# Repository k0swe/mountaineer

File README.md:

This is a build-it-yourself project at the moment. For something productized, see https://digirig.net/!

#  Mountaineer Radio Interface

This KiCAD project is a schematic for an integrated CAT and audio amateur radio interface. It's
designed with the [Lab599 Discovery TX-500](https://lab599.com/) radio in mind, but the only thing
that makes it radio-specific is the GX12 connectors for CAT and DATA. The rest of the board is a
generic USB-to-serial and audio interface and is suitable for many radios.

This is somewhat comparable to the Yaesu SCU-17 interface in that it provides both audio
and [CAT control](https://en.wikipedia.org/wiki/Computer_Aided_Transceiver). It is less like the
SignaLink USB interface which only provides audio plus a VOX-based PTT signal but not CAT control.

My design goals are to make this much like the TX-500 itself: small, lightweight and rugged enough
to be outdoors. As such, volume knobs and headphone monitor jacks are not incorporated.

Mechanical CAD drawings are hosted publicly in 
[Onshape](https://cad.onshape.com/documents/40ae2a09f3b2d7950cd3b26d/w/39e0f86d97c1d198a7f9316f/e/2142c3ad4293d2f81a75534e).

## Thank you!

I've received a lot of advice from folks about improvements to this design. Thank you to those who
have helped make this project better!

* Kari Argillander, [@teksturi](https://github.com/teksturi)
* Elías Rodríguez Martín, [@eliasrm87](https://github.com/eliasrm87)
* EEVblog Forum user [mon2](https://www.eevblog.com/forum/profile/?u=690092)
* Dave Maciorowski, [WA1JHK](https://www.qrz.com/db/WA1JHK)
* Nathan Conrad, [@pigrew](https://github.com/pigrew)
* Andreas Jochum, [@ctech4285](https://github.com/ctech4285)
* [The Gizmo Dojo](http://thegizmodojo.com/)
* [Rocky Mountain Ham Radio](https://www.rmham.org/)

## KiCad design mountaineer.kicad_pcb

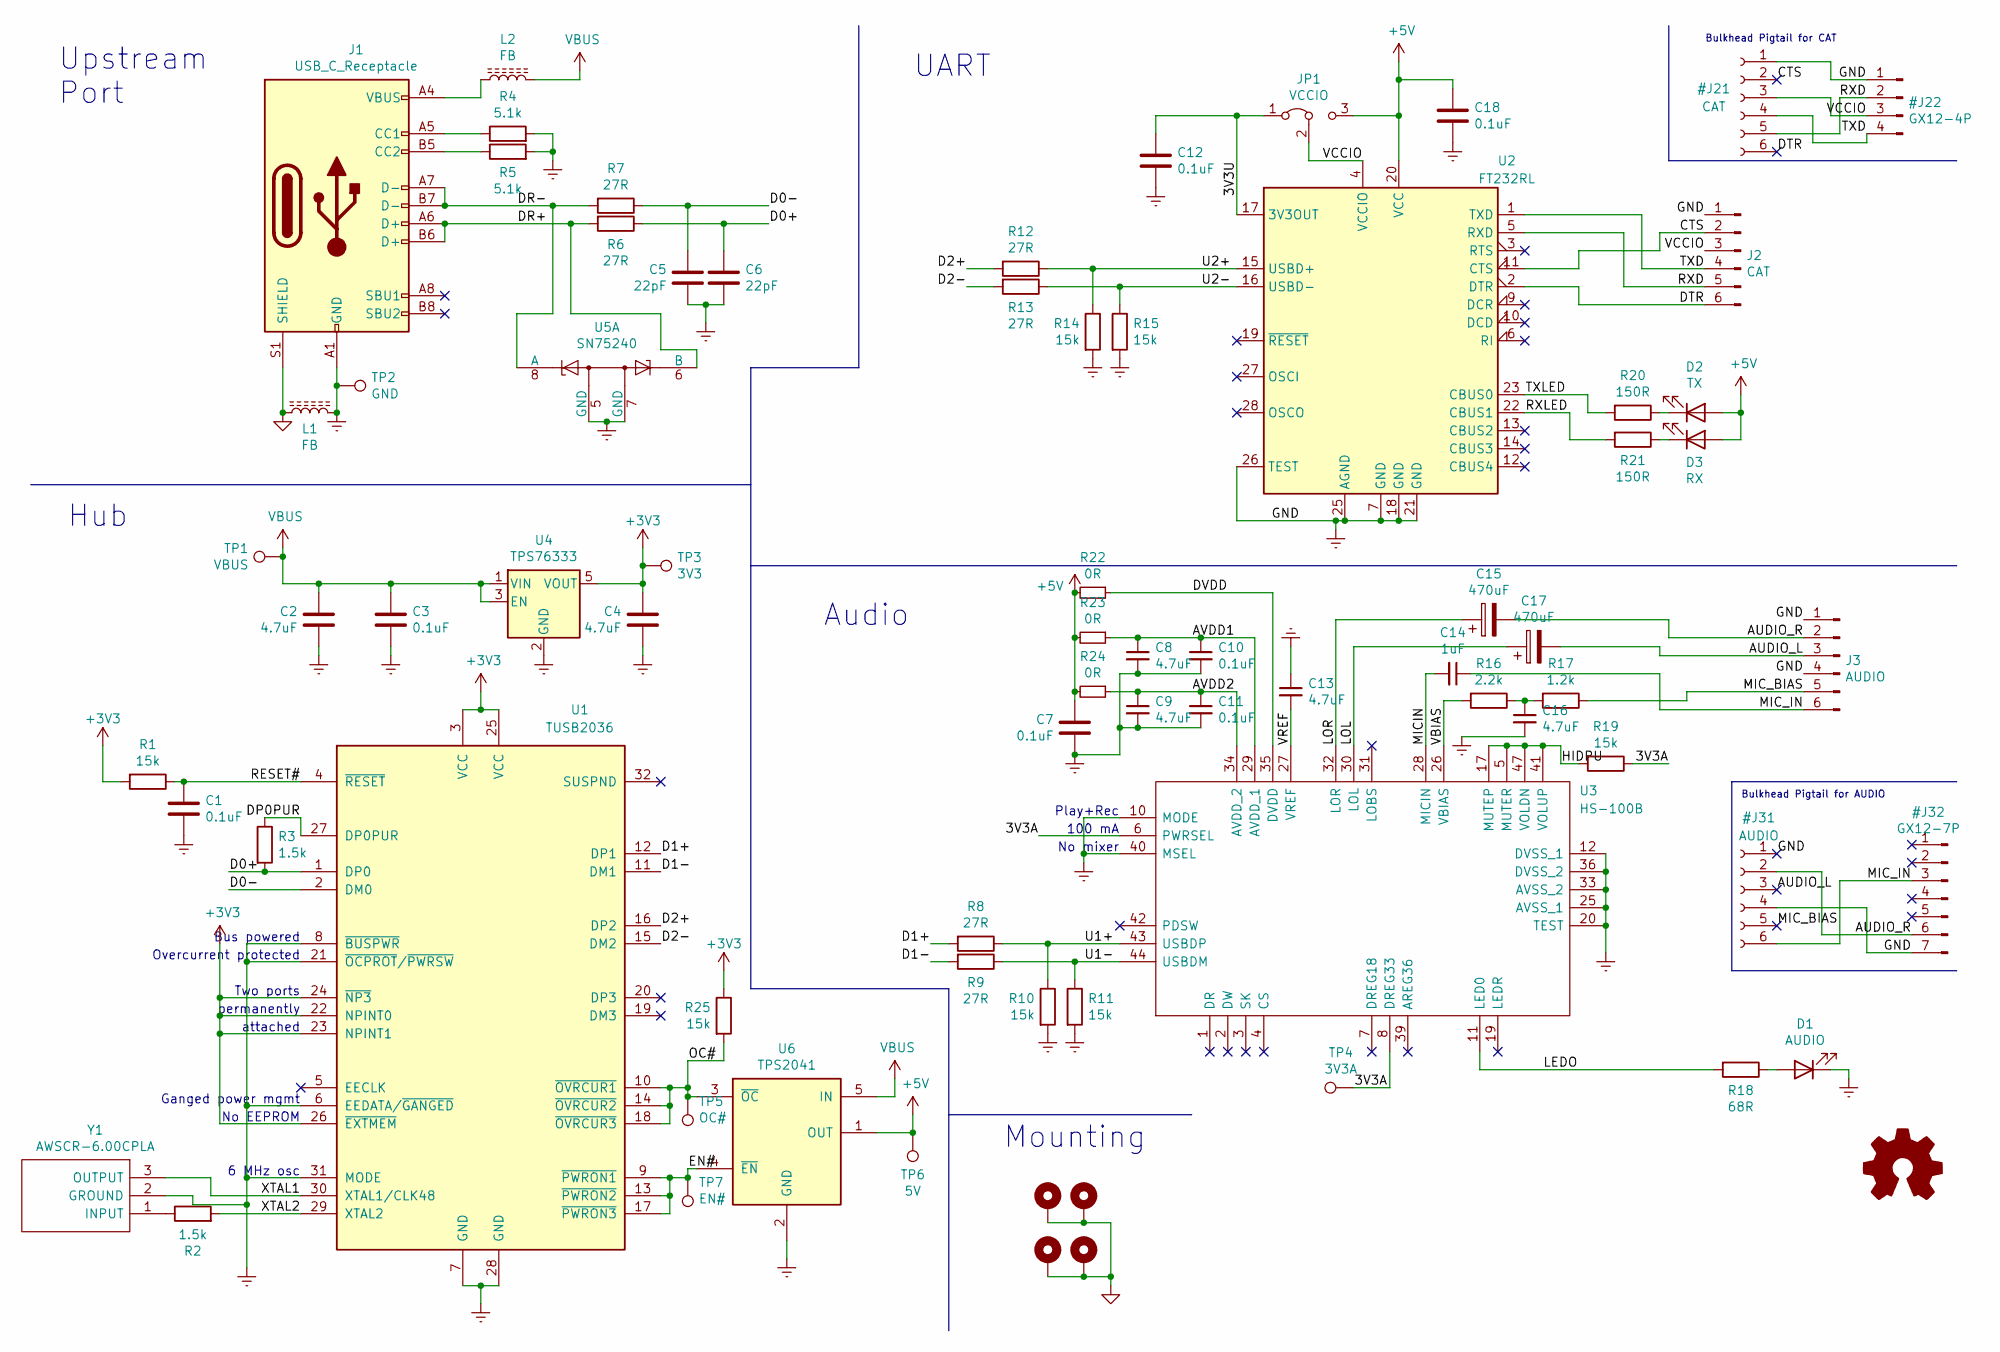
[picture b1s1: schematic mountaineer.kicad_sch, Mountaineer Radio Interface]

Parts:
C1, C3, C7, C10, C11, C12, C18: 0.1uF; C_0603_1608Metric; LCSC C1588
C2, C4, C8, C9, C13, C16: 4.7uF; C_0603_1608Metric; LCSC C19666
C5, C6: 22pF; C_0603_1608Metric; LCSC C1653
C14: 1uF; C_0603_1608Metric; LCSC C15849
C15, C17: 470uF; CAPPM7343X430N; Manufacturer_Part_Number 293D477X9010E2TE3; LCSC C232200
D1: AUDIO; LED_0603_1608Metric; LCSC C2286
D2: TX; LED_0603_1608Metric; LCSC C2286
D3: RX; LED_0603_1608Metric; LCSC C2286
H1, H2, H3, H4: MountingHole_Pad; MountingHole_2.2mm_M2_Pad
J1: USB_C_Receptacle; CUI_UJ31-CH-G-SMT-TR-67; Manufacturer_Part_Number UJ31-CH-G-SMT-TR-67
J2: CAT; JST_PH_B6B-PH-SM4-TB_1x06-1MP_P2.00mm_Vertical; Manufacturer_Part_Number B6B-PH-SM4-TB; LCSC C471518
J3: AUDIO; JST_PH_B6B-PH-SM4-TB_1x06-1MP_P2.00mm_Vertical; Manufacturer_Part_Number B6B-PH-SM4-TB; LCSC C471518
JP1: VCCIO; SolderJumper-3_P1.3mm_Bridged12_RoundedPad1.0x1.5mm
L1, L2: FB; L_0805_2012Metric; LCSC C1017
LOGO1: Logo_Open_Hardware_Small; OSHW-Logo2_9.8x8mm_Copper
R1, R10, R11, R14, R15, R19, R25: 15k; R_0603_1608Metric; LCSC C22809
R2, R3: 1.5k; R_0603_1608Metric; LCSC C22843
R4, R5: 5.1k; R_0603_1608Metric; LCSC C23186
R6, R7, R8, R9, R12, R13: 27R; R_0603_1608Metric; LCSC C25190
R16: 2.2k; R_0603_1608Metric; LCSC C4190
R17: 1.2k; R_0603_1608Metric; LCSC C22765
R18: 68R; R_0603_1608Metric; LCSC C27592
R20, R21: 150R; R_0603_1608Metric; LCSC C22808
R22, R23, R24: 0R; R_0603_1608Metric; LCSC C21189
TP1: VBUS; TestPoint_Pad_D1.0mm
TP2: GND; TestPoint_Pad_D1.0mm
TP3: 3V3; TestPoint_Pad_D1.0mm
TP4: 3V3A; TestPoint_Pad_D1.0mm
TP5: OC#; TestPoint_Pad_D1.0mm
TP6: 5V; TestPoint_Pad_D1.0mm
TP7: EN#; TestPoint_Pad_D1.0mm
U1: TUSB2036; LQFP-32_7x7mm_P0.8mm; Manufacturer_Part_Number TUSB2036VF; LCSC C43665
U2: FT232RL; SSOP-28_5.3x10.2mm_P0.65mm; Manufacturer_Part_Number FT232RL; LCSC C8690
U3: HS-100B; LQFP-48_7x7mm_P0.5mm; Manufacturer_Part_Number HS-100B; LCSC C371351
U4: TPS76333; SOT-23-5; Manufacturer_Part_Number TPS76333DBV; LCSC C7100
U5: SN75240; TSSOP-8_4.4x3mm_P0.65mm; Manufacturer_Part_Number SN75240PW; LCSC C7067
U6: TPS2041; SOT-23-5; Manufacturer_Part_Number TPS2041CDBV; LCSC C206041
Y1: AWSCR-6.00CPLA; AWSCR600CPLAC30T4; Manufacturer_Part_Number AWSCR-6.00CPLA-C30-T4

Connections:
+3V3: C4.1, R1.2, R25.1, TP3.1, U1.3 (VCC), U1.22 (NPINT0), U1.23 (NPINT1), U1.24 (~NP3), U1.25 (VCC), U1.26 (~EXTMEM), U4.5 (VOUT)
+5V: C7.1, C18.1, D2.2 (A), D3.2 (A), JP1.3 (B), R22.2, R23.2, R24.2, TP6.1, U2.20 (VCC), U6.1 (OUT)
/3V3A: R19.1, TP4.1, U3.6 (PWRSEL), U3.8 (DREG33)
/3V3U: C12.1, JP1.1 (A), U2.17 (3V3OUT)
/AVDD1: C8.1, C10.1, R23.1, U3.29 (AVDD_1)
/AVDD2: C9.1, C11.1, R24.1, U3.34 (AVDD_2)
/D0+: C6.1, R3.2, R6.1, U1.1 (DP0)
/D0-: C5.1, R7.1, U1.2 (DM0)
/D1+: R8.2, U1.12 (DP1)
/D1-: R9.2, U1.11 (DM1)
/D2+: R12.2, U1.16 (DP2)
/D2-: R13.2, U1.15 (DM2)
/DP0PUR: R3.1, U1.27 (DP0PUR)
/DR+: J1.A6 (D+), J1.B6 (D+), R6.2, U5.6 (B)
/DR-: J1.A7 (D-), J1.B7 (D-), R7.2, U5.8 (A)
/DVDD: R22.1, U3.35 (DVDD)
/EN#: TP7.1, U1.9 (~PWRON1), U1.13 (~PWRON2), U1.17 (~PWRON3), U6.4 (~EN)
/HIDPU: R19.2, U3.5 (MUTER), U3.17 (MUTEP), U3.41 (VOLUP), U3.47 (VOLDN)
/LEDO: R18.2, U3.11 (LED0)
/LOL: C17.1, U3.30 (LOL)
/LOR: C15.1, U3.32 (LOR)
/MICIN: C14.2, U3.28 (MICIN)
/OC#: R25.2, TP5.1, U1.10 (~OVRCUR1), U1.14 (~OVRCUR2), U1.18 (~OVRCUR3), U6.3 (~OC)
/RESET#: C1.1, R1.1, U1.4 (~RESET)
/RXLED: R21.2, U2.22 (CBUS1)
/TXLED: R20.2, U2.23 (CBUS0)
/U1+: R8.1, R10.1, U3.43 (USBDP)
/U1-: R9.1, R11.1, U3.44 (USBDM)
/U2+: R12.1, R14.1, U2.15 (USBD+)
/U2-: R13.1, R15.1, U2.16 (USBD-)
/VBIAS: R16.2, U3.26 (VBIAS)
/VREF: C13.2, U3.27 (VREF)
/XTAL1: U1.30 (XTAL1/CLK48), Y1.3 (OUTPUT)
/XTAL2: R2.2, U1.29 (XTAL2)
GND1: H1.1, H2.1, H3.1, H4.1, J1.S1 (SHIELD), L1.1
unnamed: C16.1, R16.1, R17.2
unnamed: D1.2 (A), R18.1
unnamed: D2.1 (K), R20.1
unnamed: D3.1 (K), R21.1
unnamed: J1.A4 (VBUS), J1.A9 (VBUS), J1.B4 (VBUS), J1.B9 (VBUS), L2.1
unnamed: J1.A5 (CC1), R4.1
unnamed: J1.B5 (CC2), R5.1
unnamed: R2.1, Y1.1 (INPUT)
VBUS: C2.1, C3.1, L2.2, TP1.1, U4.1 (VIN), U4.3 (EN), U6.5 (IN)

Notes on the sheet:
Bulkhead Pigtail for AUDIO
No mixer
Hub
Upstream Port
Audio
Ganged power mgmt
permanently
UART
attached
Play+Rec
Bulkhead Pigtail for CAT
No EEPROM
6 MHz osc
100 mA
Bus powered
Two ports
Overcurrent protected
Mounting

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
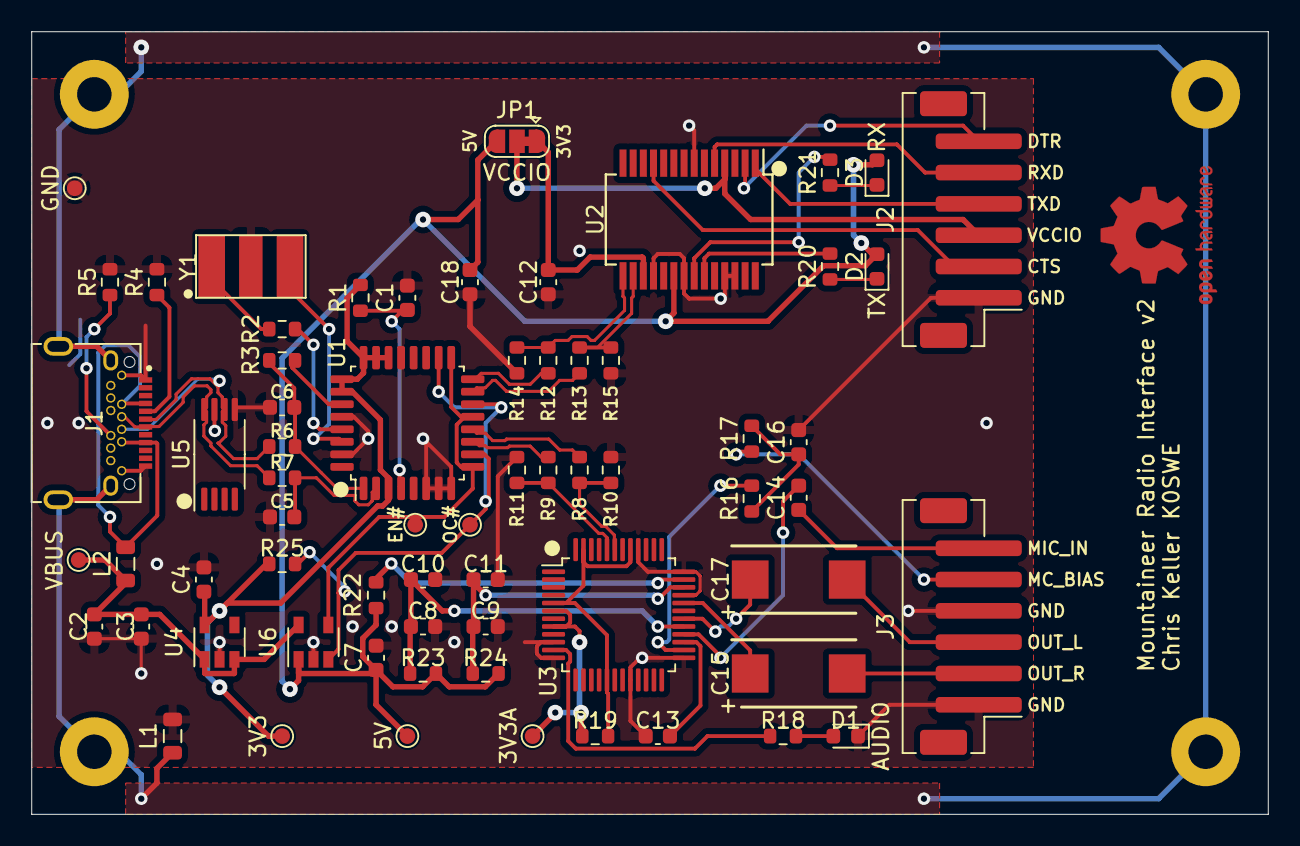
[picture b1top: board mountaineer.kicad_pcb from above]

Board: 2 copper layers, 79.0 x 50.0 mm, 71 parts (0 on the bottom side), 54 nets.

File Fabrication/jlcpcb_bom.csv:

Comment,Designator,Footprint,LCSC
1uF,C14,Capacitor_SMD:C_0603_1608Metric,C15849
470uF,"C15,C17",Vishay:CAPPM7343X430N,C232200
4.7uF,"C2,C4,C8,C9,C13,C16",Capacitor_SMD:C_0603_1608Metric,C19666 
0.1uF,"C1,C3,C7,C10,C11,C12,C18",Capacitor_SMD:C_0603_1608Metric,C1588
22pF,"C5,C6",Capacitor_SMD:C_0603_1608Metric,C1653
AUDIO,D1,LED_SMD:LED_0603_1608Metric,C2286
TX,D2,LED_SMD:LED_0603_1608Metric,C2286
RX,D3,LED_SMD:LED_0603_1608Metric,C2286
USB_C_Receptacle,J1,CUI:CUI_UJ31-CH-G-SMT-TR-67,-
CAT,J2,Connector_JST:JST_PH_B6B-PH-SM4-TB_1x06-1MP_P2.00mm_Vertical,C471518
AUDIO,J3,Connector_JST:JST_PH_B6B-PH-SM4-TB_1x06-1MP_P2.00mm_Vertical,C471518
FB,"L1,L2",Inductor_SMD:L_0805_2012Metric,C1017
15k,"R1,R10,R11,R14,R15,R19,R25",Resistor_SMD:R_0603_1608Metric,C22809
2.2k,R16,Resistor_SMD:R_0603_1608Metric,C4190
1.2k,R17,Resistor_SMD:R_0603_1608Metric,C22765
68R,R18,Resistor_SMD:R_0603_1608Metric,C27592
1.5k,"R2,R3",Resistor_SMD:R_0603_1608Metric,C22843
150R,"R20,R21",Resistor_SMD:R_0603_1608Metric,C22808
0R,"R22,R23,R24",Resistor_SMD:R_0603_1608Metric,C21189
5.1k,"R4,R5",Resistor_SMD:R_0603_1608Metric,C23186
27R,"R6,R7,R8,R9,R12,R13",Resistor_SMD:R_0603_1608Metric,C25190
TUSB2036,U1,Package_QFP:LQFP-32_7x7mm_P0.8mm,C43665
FT232RL,U2,Package_SO:SSOP-28_5.3x10.2mm_P0.65mm,C8690
CM108B,U3,Package_QFP:LQFP-48_7x7mm_P0.5mm,C371347
TPS76333,U4,Package_TO_SOT_SMD:SOT-23-5,C7100
SN75240,U5,Package_SO:TSSOP-8_4.4x3mm_P0.65mm,C7067
TPS2041,U6,Package_TO_SOT_SMD:SOT-23-5,C206041
AWSCR-6.00CPLA,Y1,Abracon:AWSCR600CPLAC30T4,-

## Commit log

2021-03-11 Add basic building blocks and datasheets
2021-03-11 Create LICENSE
2021-03-11 Add README
2021-03-11 Start using heirarchical pages, and progress on subsystems
2021-03-12 Moved clock to its own page
2021-03-12 First pass at audio
2021-03-12 First pass at pcb layout
    Not really ready to set that in stone, but wanted to get an idea of what size enclosure will work.
2021-03-14 Swap TUSB4041I for TUSB2036
    The 4041 does more than I need it to, so use the 2036 instead.
2021-03-14 Add BOM and clarify some footprints
2021-03-14 Add BOM details
2021-03-14 Replace 100 uF caps
    The ones I had selected before were only rated for 4V, and I need at least 5V (USB bus).
2021-03-15 Add a 15mm buffer for the GX12 bulkhead connectors
2021-03-15 Add ID markings on schema and pcb
2021-03-15 First pass at routing PCB
2021-03-15 Replace USB-A port with SMD
2021-03-16 Adjust USB connectors to start case CAD
2021-03-18 Reorganize onto one page
    Suggested by eevblog.com/forum user teksturi, with thanks! https://www.eevblog.com/forum/oshw/advice-on-a-custom-usb-device/msg3518118/#msg3518118
2021-03-18 Add render
2021-03-18 Add render to README
2021-03-19 Fix floating pins
2021-03-19 Add case ground
2021-03-19 Clean up HS-100B pins
    Add test points
2021-03-19 Avoid schematic cross-junction
2021-03-19 Move back case ground strip
2021-03-19 Add ESD and overcurrent protection
2021-03-20 Move 2mm away from enclosure sides
2021-03-20 Add folks to thank you list
2021-03-20 Add profile links
2021-03-22 Add mon2 to thanks list
2021-03-22 Add WA1JHK to contributors
2021-03-23 Incorporate advice
    * Remove 120uF decoupling cap for J1
    * Pull up EN4 to disable OUT4
    * Add 0ohm resistors to L/R audio lines in case I need them
    * Also, move components farther away from the enclosure edges
2021-03-23 Update assets
2021-03-26 Add pigrew to thanks list
2021-04-01 Fix JST part number
    Adafruit 4392 is horizontal, not vertical.
2021-04-01 Change 4-pin JST cable
    I can't find any 4-pin cables with no termination, and this one is cheaper.
2021-04-01 Even cheaper 4-pin JST cable
2021-04-02 Add 3D models, and various cleanup
2021-04-02 Fix crystal BOM and footprint
2021-04-03 Use standard footprint for crystal
2021-04-04 Convert BOM from one per line to grouped
2021-04-04 Use smaller dimensions capacitor
2021-04-04 Fix BOM
2021-04-05 Fix part properties
2021-04-05 Thicker 5V traces and clean up case grounds
2021-04-15 Change license to CC-BY-4.0
    CC is more conducive to open hardware than Apache
2021-04-16 Add Andreas to thank you list
2021-04-24 Remove unused OSHW logos and use basic ones
2021-05-05 Massive rework based on experience with demo boards
2021-05-05 Clean up libraries
    Since I'm spec'ing the Abracon AWSCR-CPLA resonator instead of a crystal, this resolves #5.
2021-05-05 Most footprint assignments after big rework
2021-05-05 Add CUI USB C connector
2021-05-05 Start populating new layout
2021-05-05 Start routing traces
2021-05-06 Route most of the board
    Still need to check design rules
2021-05-06 Rotate UART and fix 3D images
2021-05-06 Clean up 3D a bit
2021-05-06 Start prepping fabrication
2021-05-06 Fix up fabrication files
2021-05-06 Add more LCSC part numbers
2021-05-07 Add BOM
2021-05-08 Fix USB-C footprint
    During fabrication review, the production engineer noticed that the 5V trace intersected with the shield pads. This was because they were using F.CU and B.CU graphics which weren't getting included i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
2021-05-10 Add Onshape details
    Also add enclosure and GX12 connectors back to BOM
2021-05-11 Add initial enclosure artwork
2021-05-12 Fix up enclosure artwork
2021-05-12 Add bulkhead parts to schematic
2021-05-12 Rename project
2021-05-13 Add details to thanks
2021-05-13 Add images
2021-05-14 Add orgs to thanks list
2021-05-15 Add pullup resistor to overcurrent protection
2021-05-16 Update end cap plate drawing
2021-05-17 More realistic tolerances
2021-05-17 Update onshape pic
2021-05-22 Add logo to README
2021-05-25 Join all Enable and Overcurrent signals
    I think this is the problem that has been bothering me for several weeks. When I replaced the TPS2044B with the TPS2041B, I thought I could use any Enable and any Overcurrent signal, but in that conf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
2021-05-26 Remove VCCIO switch and add more test points
2021-06-07 Switch audio from HS100B to CM108B
    The HS-100B is getting hard to find, but the CM108B is still available.
2021-06-16 Add digirig link to README
2022-01-06 Add auto-assign-pr workflow
2023-06-02 Add renovate.json
2023-08-28 Convert to Kicad 7 project

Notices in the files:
mountaineer.kicad_pcb:
Licensed under Creative Commons CC-BY-4.0
